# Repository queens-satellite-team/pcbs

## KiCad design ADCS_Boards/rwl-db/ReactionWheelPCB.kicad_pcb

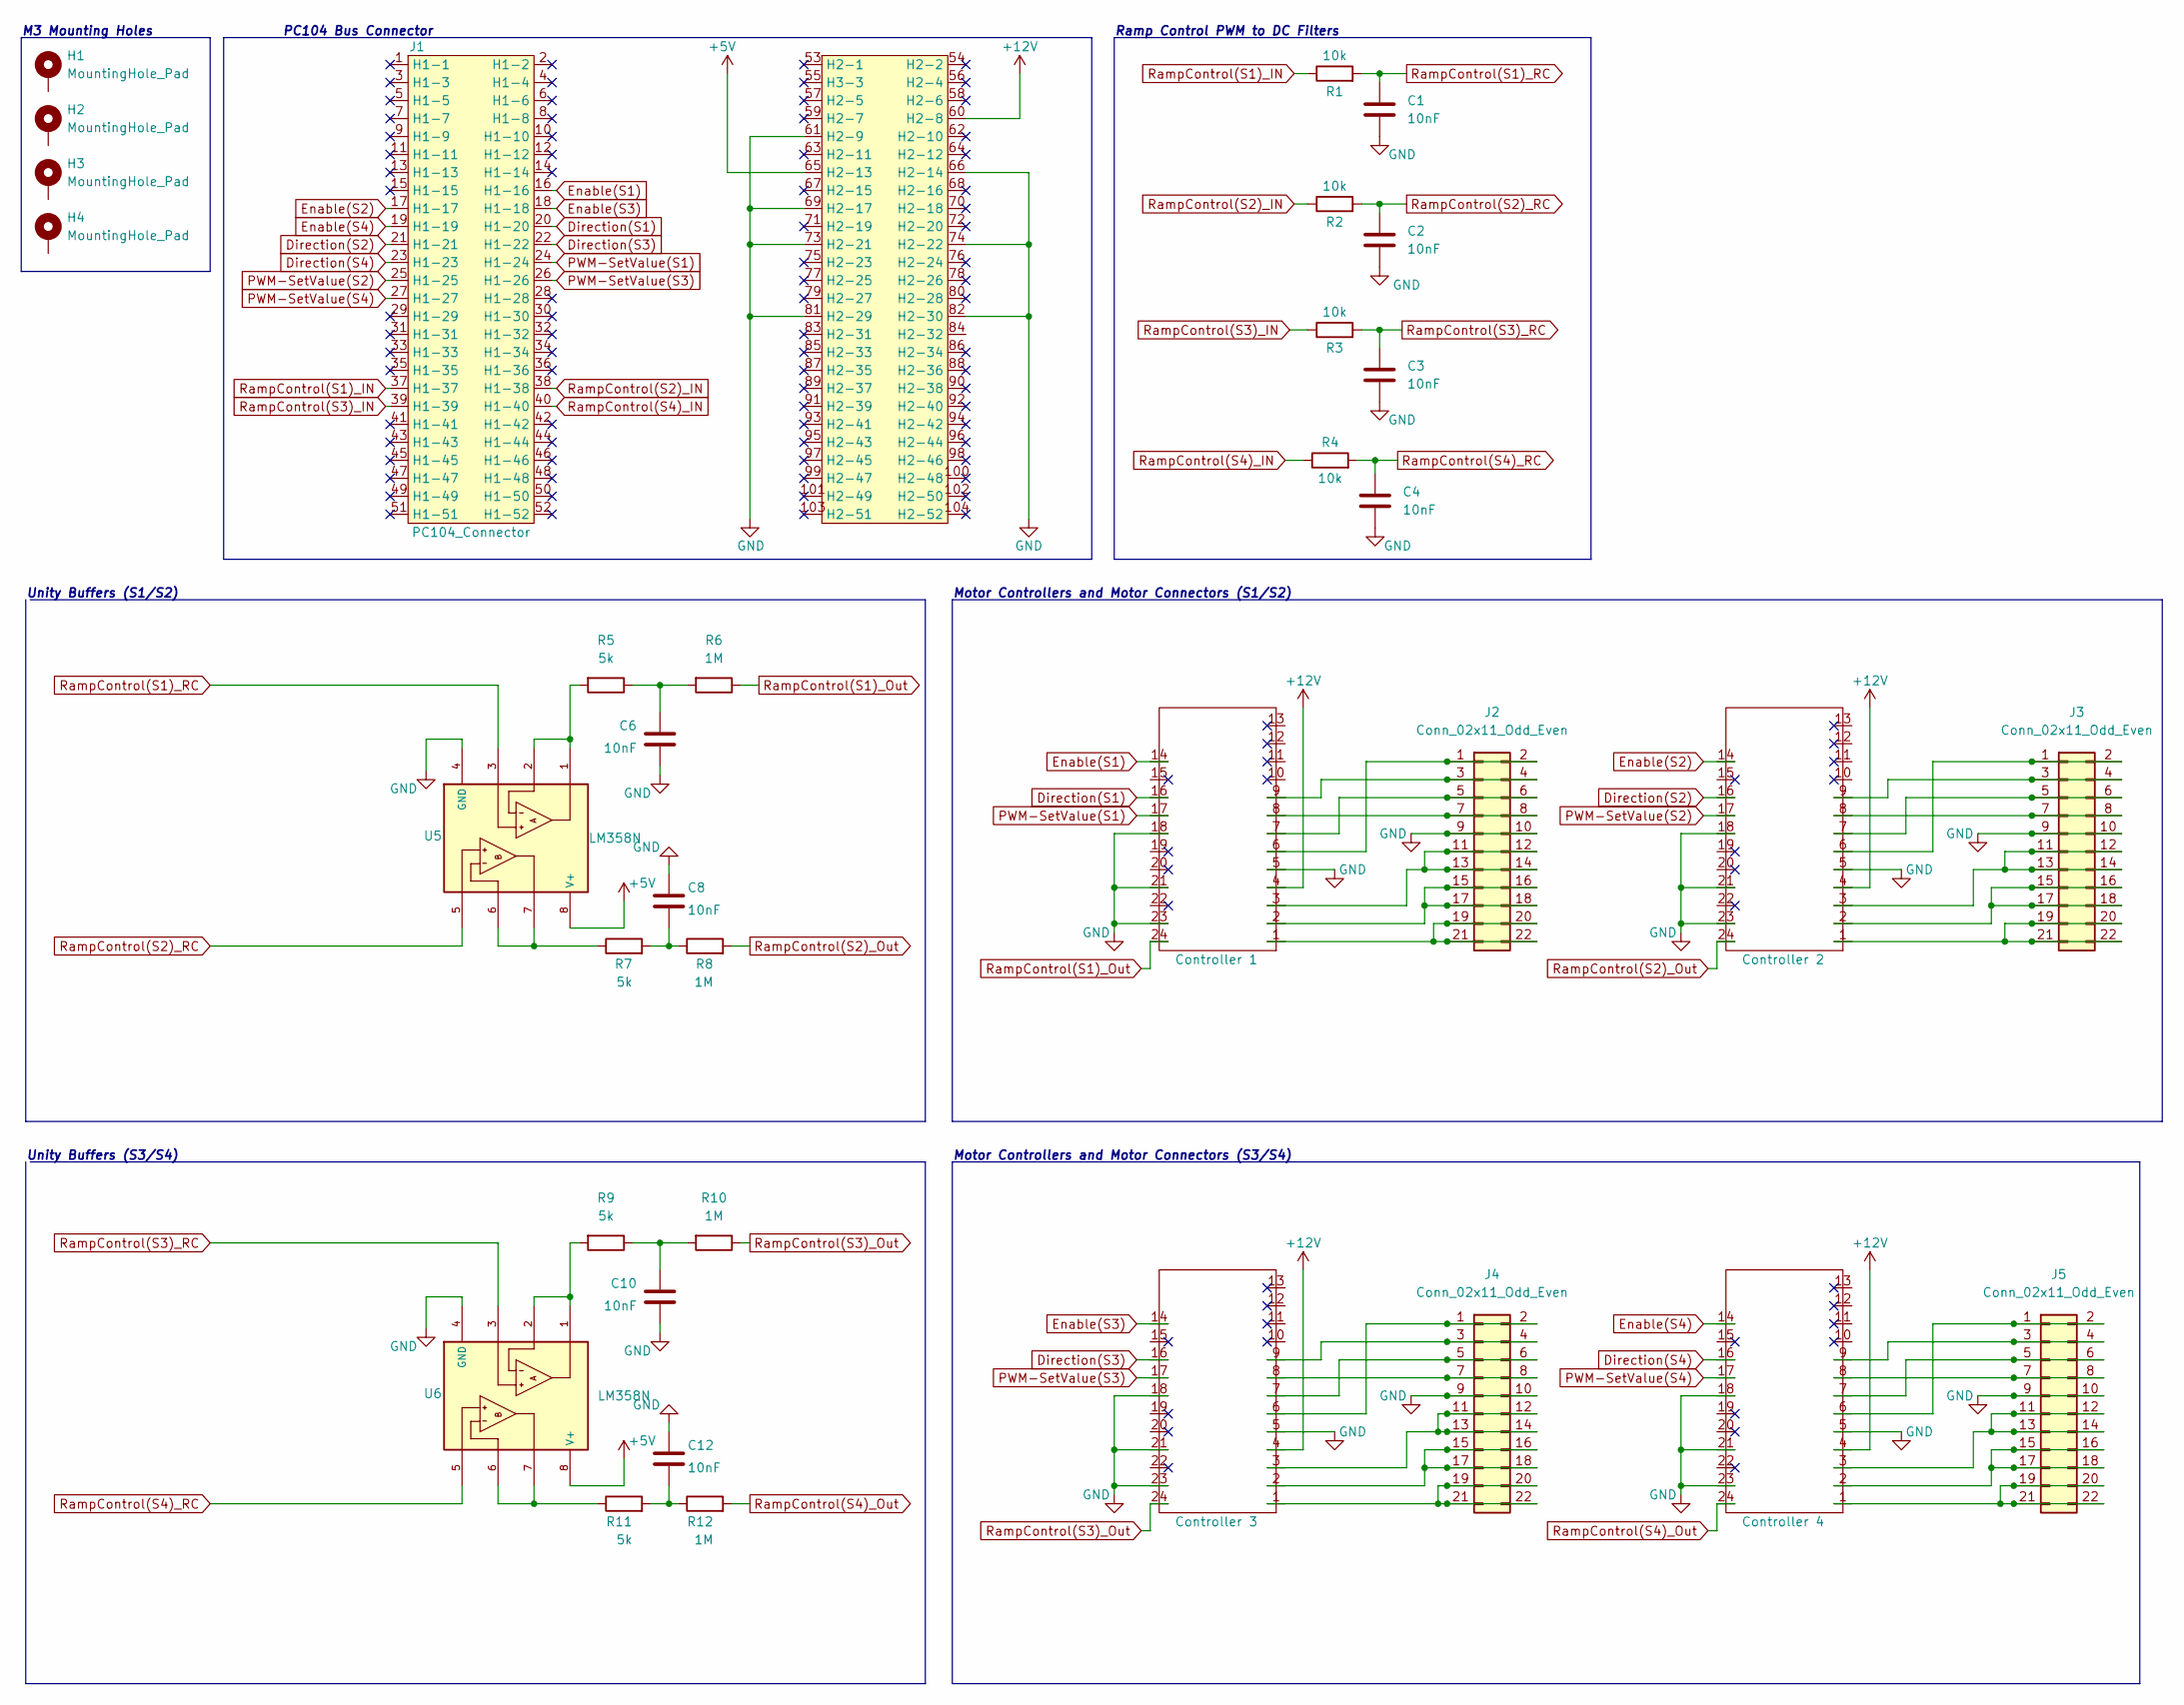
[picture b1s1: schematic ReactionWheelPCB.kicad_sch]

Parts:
C1, C2, C3, C4, C6, C8, C10, C12: 10nF; C_0603_1608Metric
H1, H2, H3, H4: MountingHole_Pad; MountingHole_3.2mm_M3_Pad_TopBottom
J1: PC104_Connector; pc104-connector
J2, J3, J4, J5: Conn_02x11_Odd_Even; 1-1734248-1-reaction-wheel-connector
R1, R2, R3, R4: 10k; R_0603_1608Metric
R5, R7, R9, R11: 5k; R_0603_1608Metric
R6, R8, R10, R12: 1M; R_0603_1608Metric
U1: Controller 1; Escon24.2
U2: Controller 2; Escon24.2
U3: Controller 3; Escon24.2
U4: Controller 4; Escon24.2
U5, U6: LM358N; DIP794W45P254L959H508Q8

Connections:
+5V: J1.65 (H2-13), U5.8 (V+), U6.8 (V+)
+12V: J1.60 (H2-8), U1.4, U2.4, U3.4, U4.4
Direction(S1): J1.20 (H1-20), U1.16
Direction(S2): J1.21 (H1-21), U2.16
Direction(S3): J1.22 (H1-22), U3.16
Direction(S4): J1.23 (H1-23), U4.16
Enable(S1): J1.16 (H1-16), U1.14
Enable(S2): J1.17 (H1-17), U2.14
Enable(S3): J1.18 (H1-18), U3.14
Enable(S4): J1.19 (H1-19), U4.14
GND: C1.1, C2.1, C3.1, C4.1, C6.1, C8.1, C10.1, C12.1, J1.61 (H2-9), J1.66 (H2-14), J1.69 (H2-17), J1.73 (H2-21), J1.74 (H2-22), J1.81 (H2-29), J1.82 (H2-30), J2.9, J2.10, J3.9, J3.10, J4.9, J4.10, J5.9, J5.10, U1.5, U1.18, U1.21, U1.23, U2.5, U2.18, U2.21, U2.23, U3.5, U3.18, U3.21, U3.23, U4.5, U4.18, U4.21, U4.23, U5.4 (GND), U6.4 (GND)
unnamed: C6.2, R5.1, R6.2
unnamed: C8.2, R7.2, R8.1
unnamed: C10.2, R9.1, R10.2
unnamed: C12.2, R11.2, R12.1
unnamed: R5.2, U5.1, U5.2
unnamed: R7.1, U5.6, U5.7
unnamed: R9.2, U6.1, U6.2
unnamed: R11.1, U6.6, U6.7
unnamed: J2.19, J2.20, J2.21, J2.22, U1.1
unnamed: J2.15, J2.16, J2.17, J2.18, U1.2
unnamed: J2.11, J2.12, J2.13, J2.14, U1.3
unnamed: J2.1, J2.2, U1.6
unnamed: J2.5, J2.6, U1.7
unnamed: J2.7, J2.8, U1.8
unnamed: J2.3, J2.4, U1.9
unnamed: J3.19, J3.20, J3.21, J3.22, U2.1
unnamed: J3.15, J3.16, J3.17, J3.18, U2.2
unnamed: J3.11, J3.12, J3.13, J3.14, U2.3
unnamed: J3.1, J3.2, U2.6
unnamed: J3.5, J3.6, U2.7
unnamed: J3.7, J3.8, U2.8
unnamed: J3.3, J3.4, U2.9
unnamed: J4.19, J4.20, J4.21, J4.22, U3.1
unnamed: J4.15, J4.16, J4.17, J4.18, U3.2
unnamed: J4.11, J4.12, J4.13, J4.14, U3.3
unnamed: J4.1, J4.2, U3.6
unnamed: J4.5, J4.6, U3.7
unnamed: J4.7, J4.8, U3.8
unnamed: J4.3, J4.4, U3.9
unnamed: J5.19, J5.20, J5.21, J5.22, U4.1
unnamed: J5.15, J5.16, J5.17, J5.18, U4.2
unnamed: J5.11, J5.12, J5.13, J5.14, U4.3
unnamed: J5.1, J5.2, U4.6
unnamed: J5.5, J5.6, U4.7
unnamed: J5.7, J5.8, U4.8
unnamed: J5.3, J5.4, U4.9
PWM-SetValue(S1): J1.24 (H1-24), U1.17
PWM-SetValue(S2): J1.25 (H1-25), U2.17
PWM-SetValue(S3): J1.26 (H1-26), U3.17
PWM-SetValue(S4): J1.27 (H1-27), U4.17
RampControl(S1)_IN: J1.37 (H1-37), R1.1
RampControl(S1)_Out: R6.1, U1.24
RampControl(S1)_RC: C1.2, R1.2, U5.3
RampControl(S2)_IN: J1.38 (H1-38), R2.1
RampControl(S2)_Out: R8.2, U2.24
RampControl(S2)_RC: C2.2, R2.2, U5.5
RampControl(S3)_IN: J1.39 (H1-39), R3.1
RampControl(S3)_Out: R10.1, U3.24
RampControl(S3)_RC: C3.2, R3.2, U6.3
RampControl(S4)_IN: J1.40 (H1-40), R4.1
RampControl(S4)_Out: R12.2, U4.24
RampControl(S4)_RC: C4.2, R4.2, U6.5

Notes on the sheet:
Motor Controllers and Motor Connectors (S3/S4)
M3 Mounting Holes
Unity Buffers (S3/S4)
Motor Controllers and Motor Connectors (S1/S2)
PC104 Bus Connector
Ramp Control PWM to DC Filters
Unity Buffers (S1/S2)

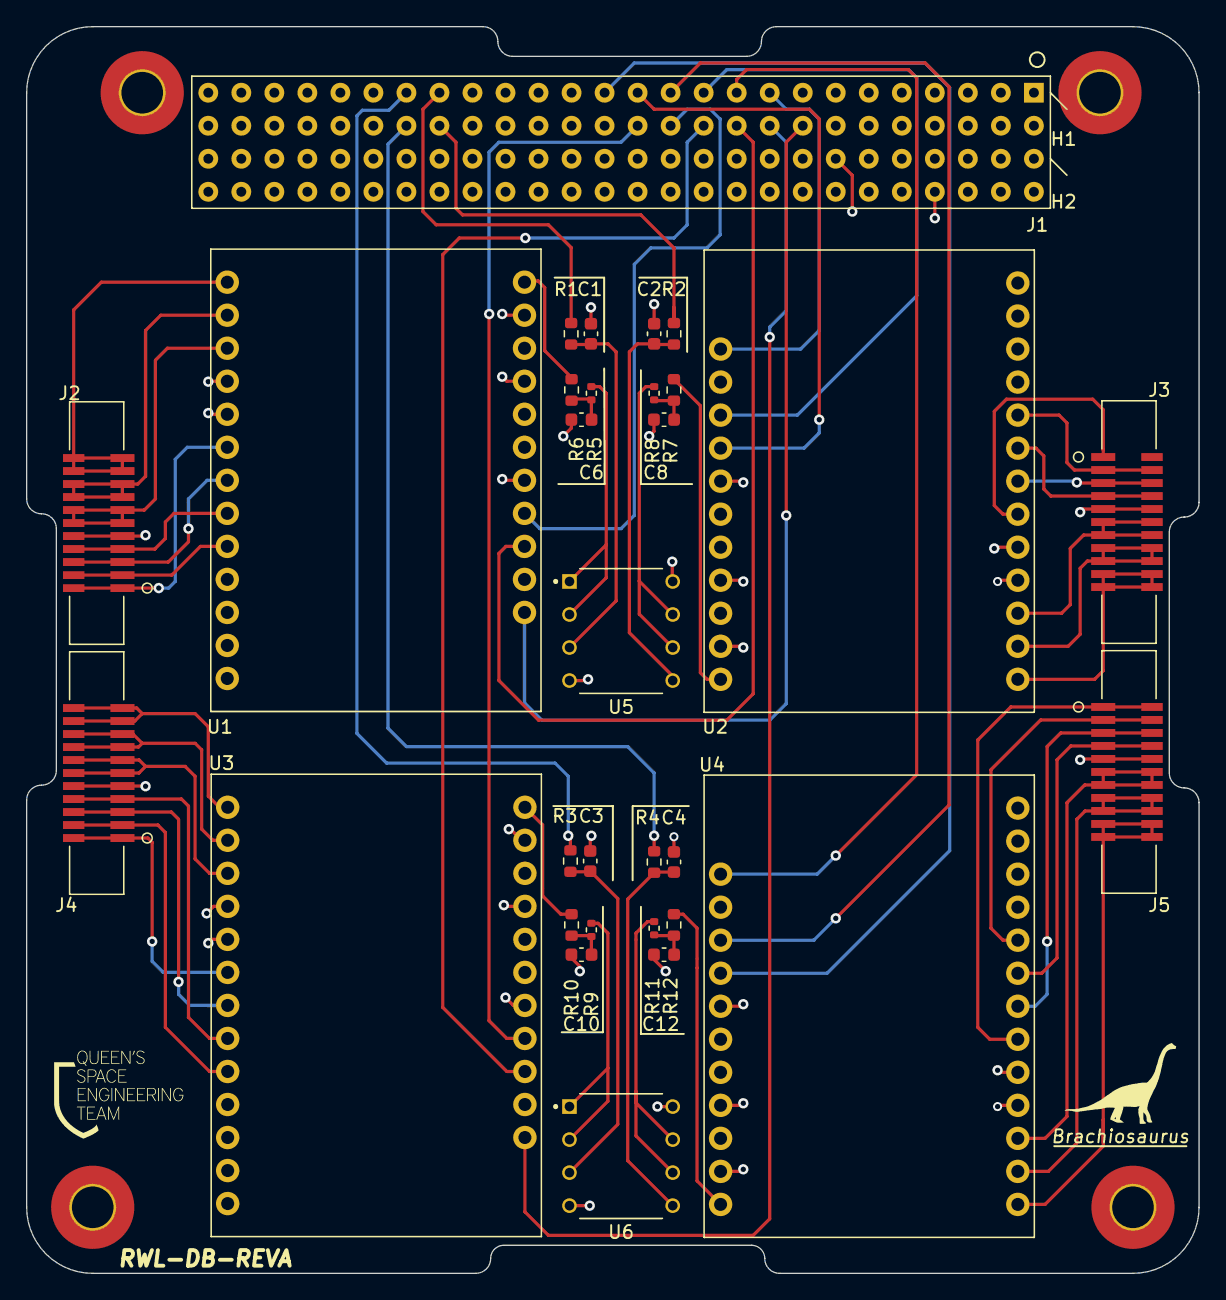
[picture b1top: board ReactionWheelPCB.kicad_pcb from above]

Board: 4 copper layers, 90.2 x 95.9 mm, 36 parts (0 on the bottom side), 63 nets.

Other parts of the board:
Brachiosaurus: LOGO

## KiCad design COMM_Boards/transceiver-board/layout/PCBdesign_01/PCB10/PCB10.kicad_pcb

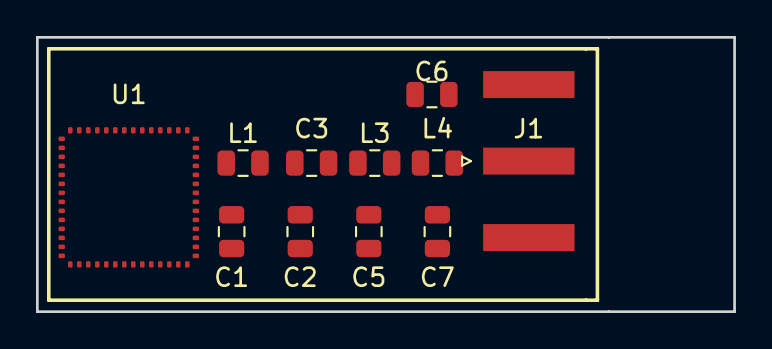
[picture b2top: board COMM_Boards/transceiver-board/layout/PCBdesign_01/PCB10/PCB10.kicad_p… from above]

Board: 2 copper layers, 38.7 x 15.2 mm, 11 parts (0 on the bottom side), 7 nets, no tracks yet.

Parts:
C1, C2: 10pf; C_0805_2012Metric
C3: 2.4pF; C_0805_2012Metric
C5, C6: 15pF; C_0805_2012Metric
C7: 8.2pF; C_0805_2012Metric
J1: Conn_Coaxial_Power; SMA_Amphenol_132289_EdgeMount
L1: 22nH; L_0805_2012Metric
L3, L4: 12nH; L_0805_2012Metric
U1: MKW01Z128

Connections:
+3V3: U1.19, U1.35, U1.43, U1.55
GND: C1.1, C2.2, C5.2, C7.2, U1.3, U1.4, U1.20, U1.36, U1.38, U1.40
unnamed: C1.2, L1.1, U1.42
unnamed: C2.1, C3.2, L1.2, U1.39
unnamed: C3.1, L3.1
unnamed: C5.1, C6.2, L3.2, L4.1
unnamed: C6.1, C7.1, J1.1, L4.2

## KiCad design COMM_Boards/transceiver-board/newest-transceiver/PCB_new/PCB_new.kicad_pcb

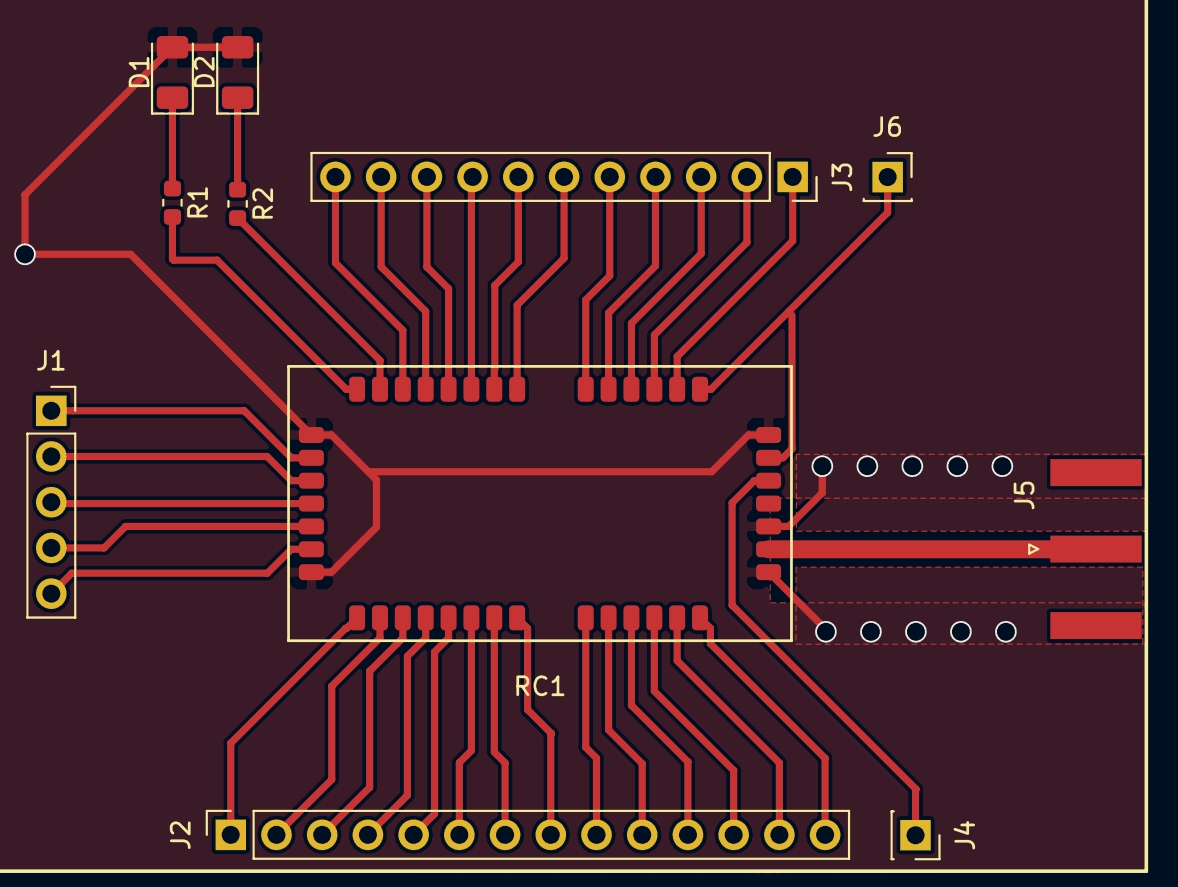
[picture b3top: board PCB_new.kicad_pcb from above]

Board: 2 copper layers, 11 parts (0 on the bottom side), 38 nets.

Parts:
D1, D2: LED; LED_1206_3216Metric
J1: Conn_01x05_Male; PinSocket_1x05_P2.54mm_Vertical
J2: Conn_01x14_Male; PinSocket_1x14_P2.54mm_Vertical
J3: Conn_01x11_Male; PinSocket_1x11_P2.54mm_Vertical
J4, J6: Conn_01x01_Male; PinSocket_1x01_P2.54mm_Vertical
J5: Conn_Coaxial_Power; SMA_Amphenol_132289_EdgeMount
R1, R2: R; R_0603_1608Metric
RC1: RC17xxHP

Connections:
GND: D1.2, D2.2, RC1.1, RC1.7, RC1.8, RC1.10, RC1.14
unnamed: D1.1, R1.1
unnamed: D2.1, R2.1
unnamed: J1.1, RC1.2
unnamed: J1.2, RC1.3
unnamed: J1.3, RC1.4
unnamed: J1.4, RC1.5
unnamed: J1.5, RC1.6
unnamed: J2.1, RC1.15
unnamed: J2.2, RC1.16
unnamed: J2.3, RC1.17
unnamed: J2.4, RC1.18
unnamed: J2.5, RC1.19
unnamed: J2.6, RC1.20
unnamed: J2.7, RC1.21
unnamed: J2.8, RC1.22
unnamed: J2.9, RC1.32
unnamed: J2.10, RC1.34
unnamed: J2.11, RC1.36
unnamed: J2.12, RC1.38
unnamed: J2.13, RC1.40
unnamed: J2.14, RC1.42
unnamed: J3.1, RC1.39
unnamed: J3.2, RC1.37
unnamed: J3.3, RC1.35
unnamed: J3.4, RC1.33
unnamed: J3.5, RC1.31
unnamed: J3.6, RC1.23
unnamed: J3.7, RC1.24
unnamed: J3.8, RC1.25
unnamed: J3.9, RC1.26
unnamed: J3.10, RC1.27
unnamed: J3.11, RC1.28
unnamed: J4.1, RC1.12
unnamed: J5.1, RC1.9
unnamed: R1.2, RC1.30
unnamed: R2.2, RC1.29
VCC: J6.1, RC1.13, RC1.41

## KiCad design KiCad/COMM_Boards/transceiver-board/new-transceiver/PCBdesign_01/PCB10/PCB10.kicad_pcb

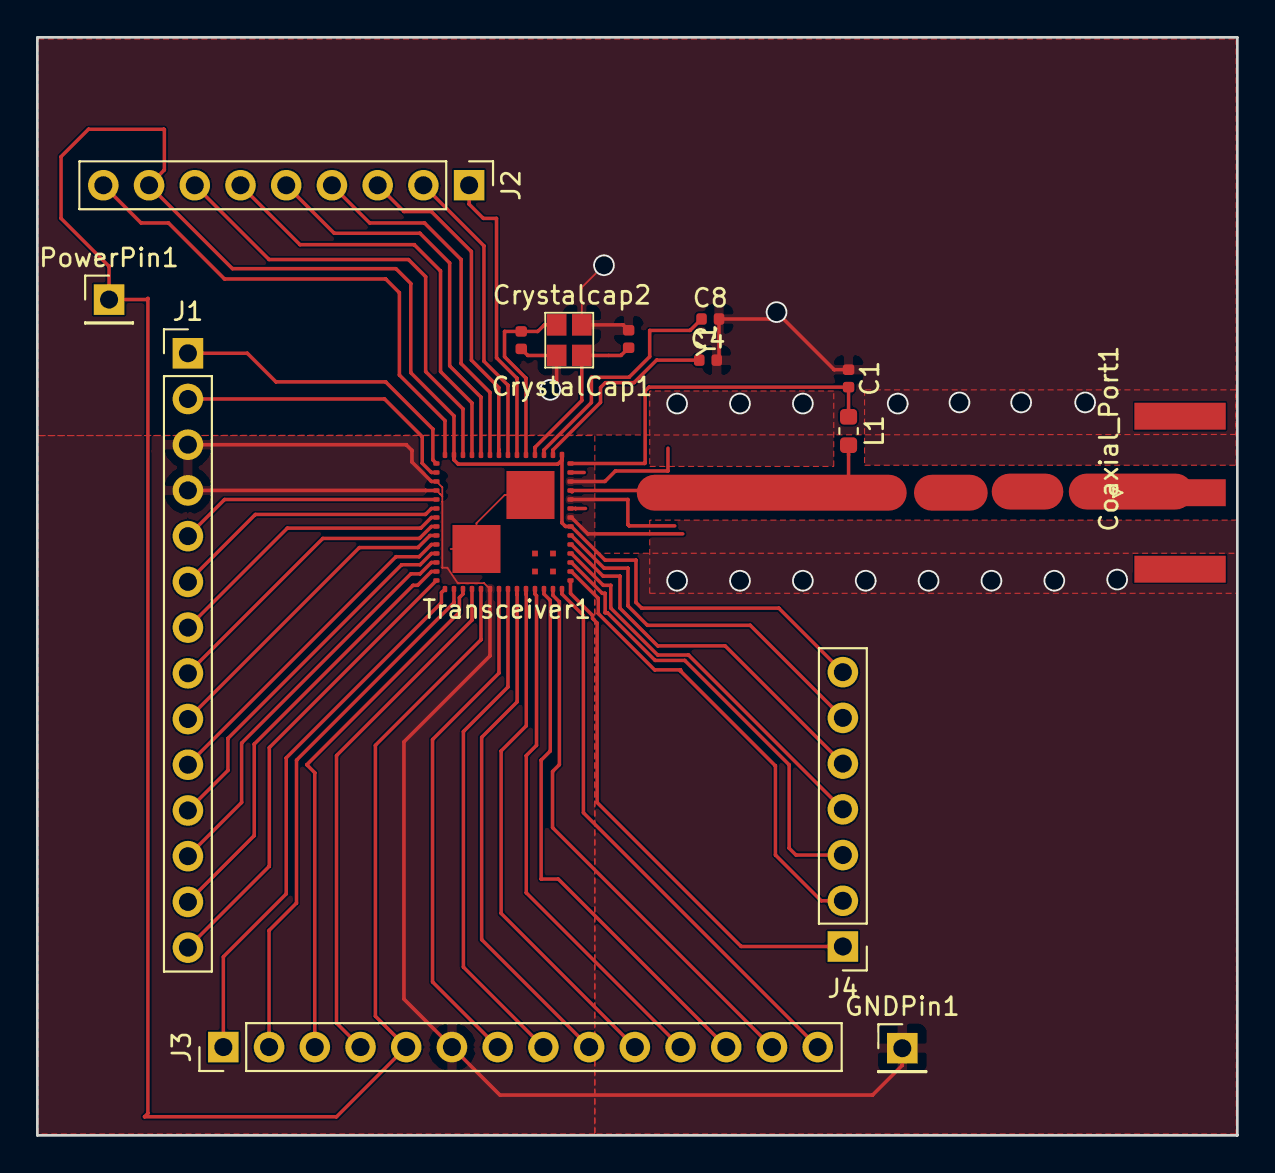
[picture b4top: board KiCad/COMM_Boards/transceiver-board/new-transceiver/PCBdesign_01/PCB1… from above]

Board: 2 copper layers, 66.7 x 61.0 mm, 15 parts (0 on the bottom side), 46 nets.

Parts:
C1: 10pf; C_0402_1005Metric
C4, C8: 100nF; C_0402_1005Metric
Coaxial_Port1: Conn_Coaxial_Power; SMA_Amphenol_132289_EdgeMount
CrystalCap1: CAP; C_0402_1005Metric
Crystalcap2: CAP; C_0402_1005Metric
GNDPin1: Conn_01x01_Male; PinHeader_1x01_P2.54mm_Vertical
J1, J3: Conn_01x14_Male; PinHeader_1x14_P2.54mm_Vertical
J2: Conn_01x09_Male; PinHeader_1x09_P2.54mm_Vertical
J4: Conn_01x07_Male; PinHeader_1x07_P2.54mm_Vertical
L1: 22nH; L_0603_1608Metric
PowerPin1: Conn_01x01_Male; PinHeader_1x01_P2.54mm_Vertical
Transceiver1: MKW01Z128_MKW01Z128; MKW01Z128
Y1: Crystal_GND24; SER3801CT-ND

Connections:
GND: C1.1, C4.2, C8.2, CrystalCap1.2, Crystalcap2.2, GNDPin1.1, J1.3, J1.4, J3.6, Transceiver1.3, Transceiver1.4, Transceiver1.20, Transceiver1.36, Transceiver1.38, Transceiver1.40, Y1.2, Y1.4
unnamed: C1.2, L1.1, Transceiver1.42
unnamed: L1.2, Transceiver1.39
unnamed: C4.1, Transceiver1.44
unnamed: C8.1, Transceiver1.45
unnamed: CrystalCap1.1, Transceiver1.46, Y1.1
unnamed: Crystalcap2.1, Transceiver1.47, Y1.3
unnamed: J1.1, Transceiver1.1
unnamed: J1.2, Transceiver1.2
unnamed: J1.5, Transceiver1.5
unnamed: J1.6, Transceiver1.6
unnamed: J1.7, Transceiver1.7
unnamed: J1.8, Transceiver1.8
unnamed: J1.9, Transceiver1.9
unnamed: J1.10, Transceiver1.10
unnamed: J1.11, Transceiver1.11
unnamed: J1.12, Transceiver1.12
unnamed: J1.13, Transceiver1.13
unnamed: J1.14, Transceiver1.14
unnamed: J2.1, Transceiver1.48
unnamed: J2.2, Transceiver1.49
unnamed: J2.3, Transceiver1.50
unnamed: J2.4, Transceiver1.51
unnamed: J2.5, Transceiver1.52
unnamed: J2.6, Transceiver1.53
unnamed: J2.7, Transceiver1.54
unnamed: J2.9, Transceiver1.56
unnamed: J3.1, Transceiver1.15
unnamed: J3.2, Transceiver1.16
unnamed: J3.3, Transceiver1.17
unnamed: J3.4, Transceiver1.18
unnamed: J3.7, Transceiver1.21
unnamed: J3.8, Transceiver1.22
unnamed: J3.9, Transceiver1.23
unnamed: J3.10, Transceiver1.24
unnamed: J3.11, Transceiver1.25
unnamed: J3.12, Transceiver1.26
unnamed: J3.13, Transceiver1.27
unnamed: J3.14, Transceiver1.28
unnamed: J4.1, Transceiver1.29
unnamed: J4.2, Transceiver1.30
unnamed: J4.3, Transceiver1.31
unnamed: J4.4, Transceiver1.32
unnamed: J4.5, Transceiver1.33
unnamed: J4.6, Transceiver1.34
POWER: J2.8, J3.5, J4.7, PowerPin1.1, Transceiver1.19, Transceiver1.35, Transceiver1.43, Transceiver1.55

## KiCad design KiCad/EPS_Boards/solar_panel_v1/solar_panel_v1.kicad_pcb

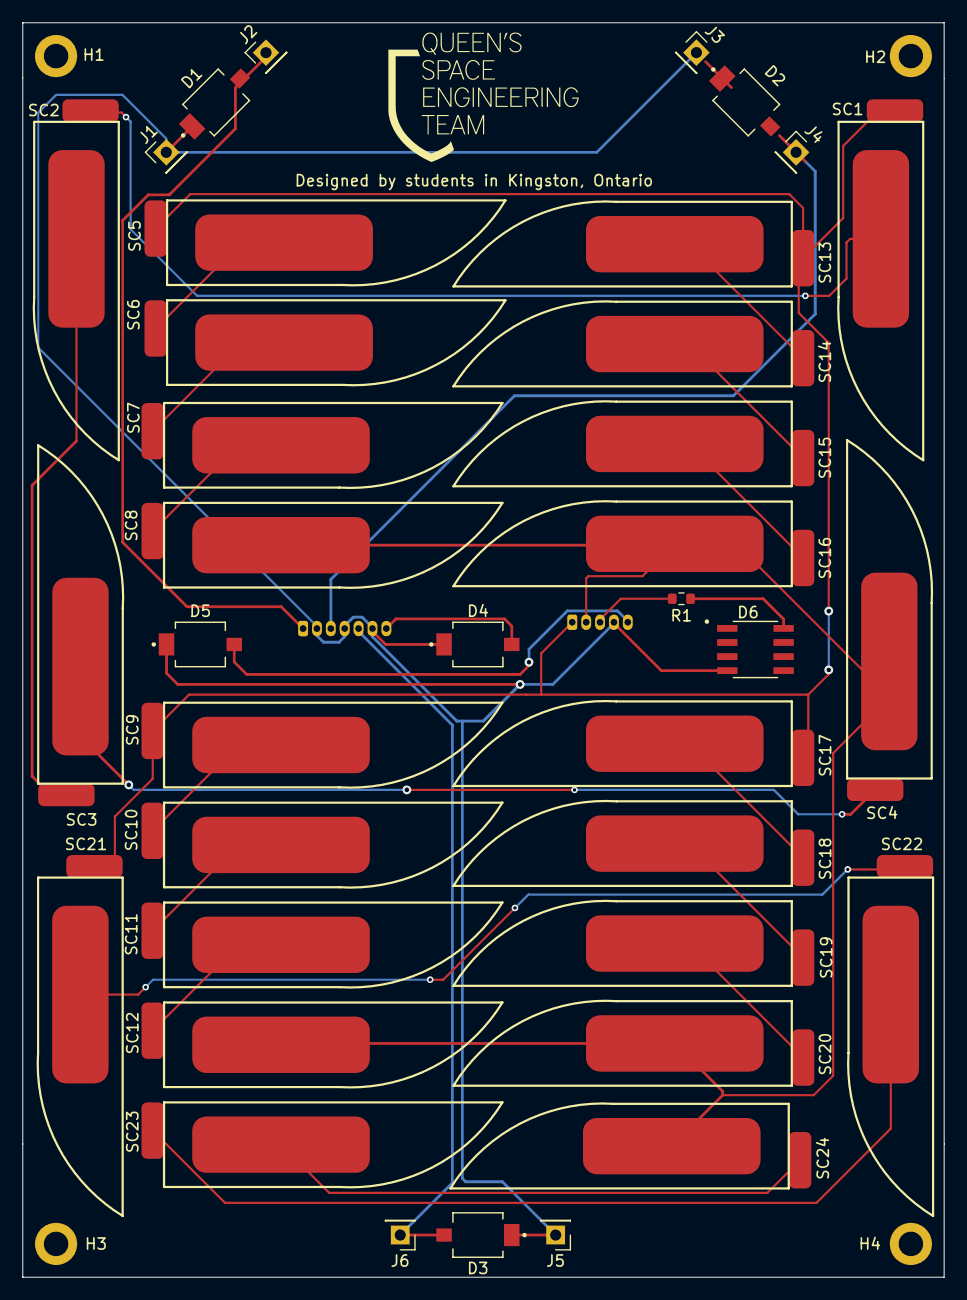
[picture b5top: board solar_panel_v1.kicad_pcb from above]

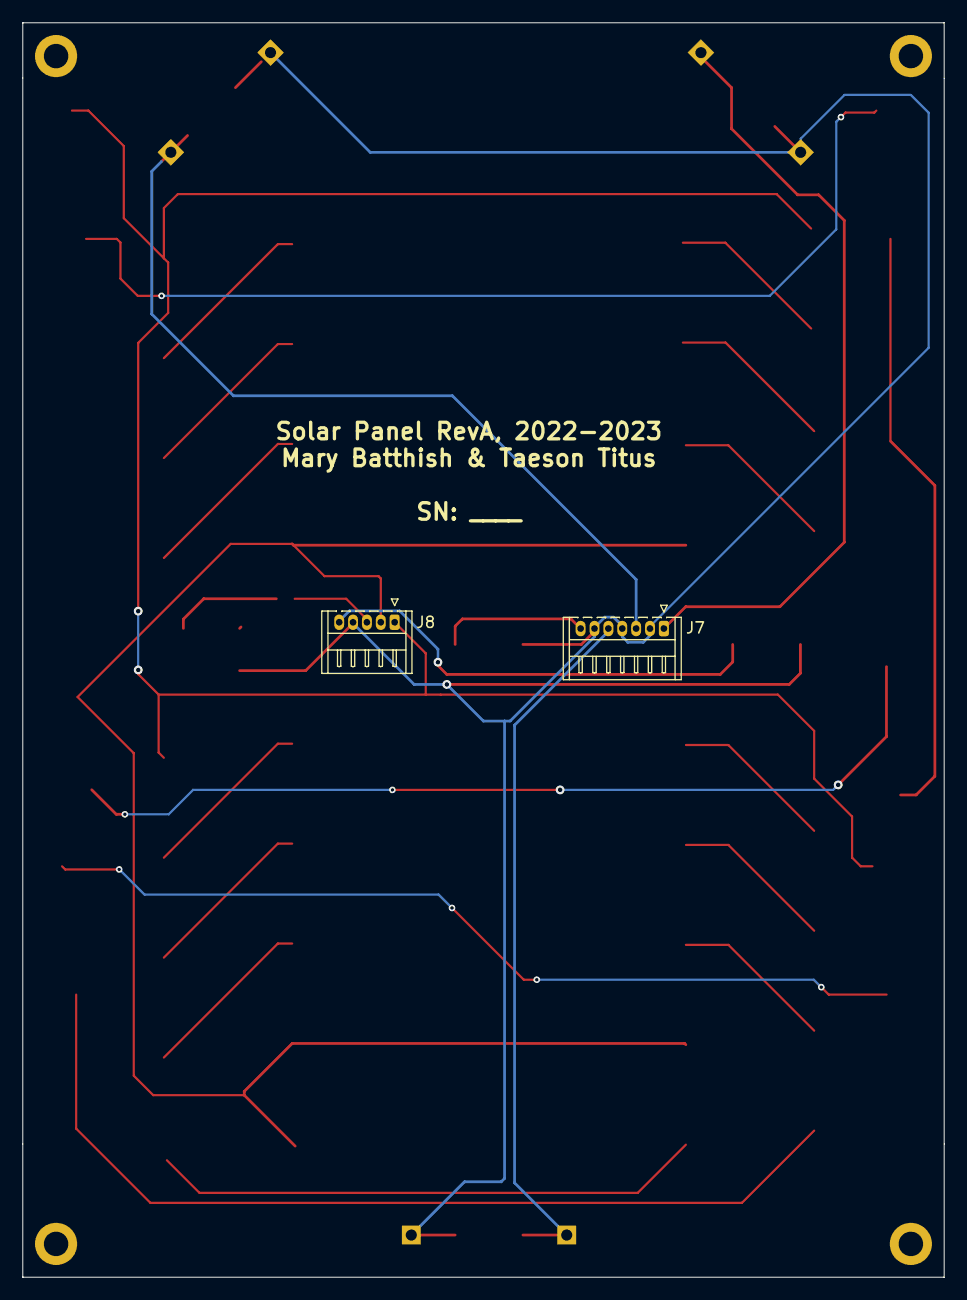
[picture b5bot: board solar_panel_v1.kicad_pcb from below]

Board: 2 copper layers, 83.0 x 113.0 mm, 43 parts (2 on the bottom side), 27 nets.

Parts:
D1, D2, D3, D4, D5: D_Photo; DIO_SFH_2430-Z
D6: D_Temp; SOIC127P600X175-8N
H1, H2, H3, H4: MountingHole; MountingHole_2.2mm_M2_DIN965_Pad
J1, J2, J3, J4, J5, J6: Conn_01x01; PinHeader_1x01_P2.54mm_Vertical
J7: DF13-7P-1.25DS(20); Hirose_DF13-07P-1.25DS_1x07_P1.25mm_Horizontal
J8: DF-13-5P-1.25DS; Hirose_DF13-05P-1.25DS_1x05_P1.25mm_Horizontal
R1: 0; R_0603_1608Metric
SC1, SC2, SC3, SC4, SC5, SC6, SC7, SC8, SC9, SC10, SC11, SC12, SC13, SC14, SC15, SC16, SC17, SC18, SC19, SC20, SC21, SC22, SC23, SC24: Solar_Cell; TrisolX_Solar_Cell

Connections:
ADSC_PD_1: D1.1 (K), J2.1
ADSC_PD_2: D2.1 (K), J4.1
ADSC_PD_3: D3.1 (K), J6.1
ARRAY_PWR: J8.1, SC1.1 (+), SC5.1 (+), SC9.1 (+), SC13.1 (+), SC17.1 (+), SC21.1 (+)
ARRAY_RTN: J8.2, SC4.2 (-), SC8.2 (-), SC12.2 (-), SC16.2 (-), SC20.2 (-), SC24.2 (-)
EPS_PD_1: D5.1 (K), J8.5
EPS_TMP_1: J8.3, R1.2
GND: D1.2 (A), D2.2 (A), D3.2 (A), D4.2 (A), D5.2 (A), D6.4, J1.1, J3.2, J5.1, J7.2, J7.4, J7.6, J8.4
unnamed: D6.8, R1.1
unnamed: SC1.2 (-), SC2.1 (+)
unnamed: SC2.2 (-), SC3.1 (+)
unnamed: SC3.2 (-), SC4.1 (+)
unnamed: SC5.2 (-), SC6.1 (+)
unnamed: SC6.2 (-), SC7.1 (+)
unnamed: SC7.2 (-), SC8.1 (+)
unnamed: SC9.2 (-), SC10.1 (+)
unnamed: SC10.2 (-), SC11.1 (+)
unnamed: SC11.2 (-), SC12.1 (+)
unnamed: SC13.2 (-), SC14.1 (+)
unnamed: SC14.2 (-), SC15.1 (+)
unnamed: SC15.2 (-), SC16.1 (+)
unnamed: SC17.2 (-), SC18.1 (+)
unnamed: SC18.2 (-), SC19.1 (+)
unnamed: SC19.2 (-), SC20.1 (+)
unnamed: SC21.2 (-), SC22.1 (+)
unnamed: SC22.2 (-), SC23.1 (+)
unnamed: SC23.2 (-), SC24.1 (+)

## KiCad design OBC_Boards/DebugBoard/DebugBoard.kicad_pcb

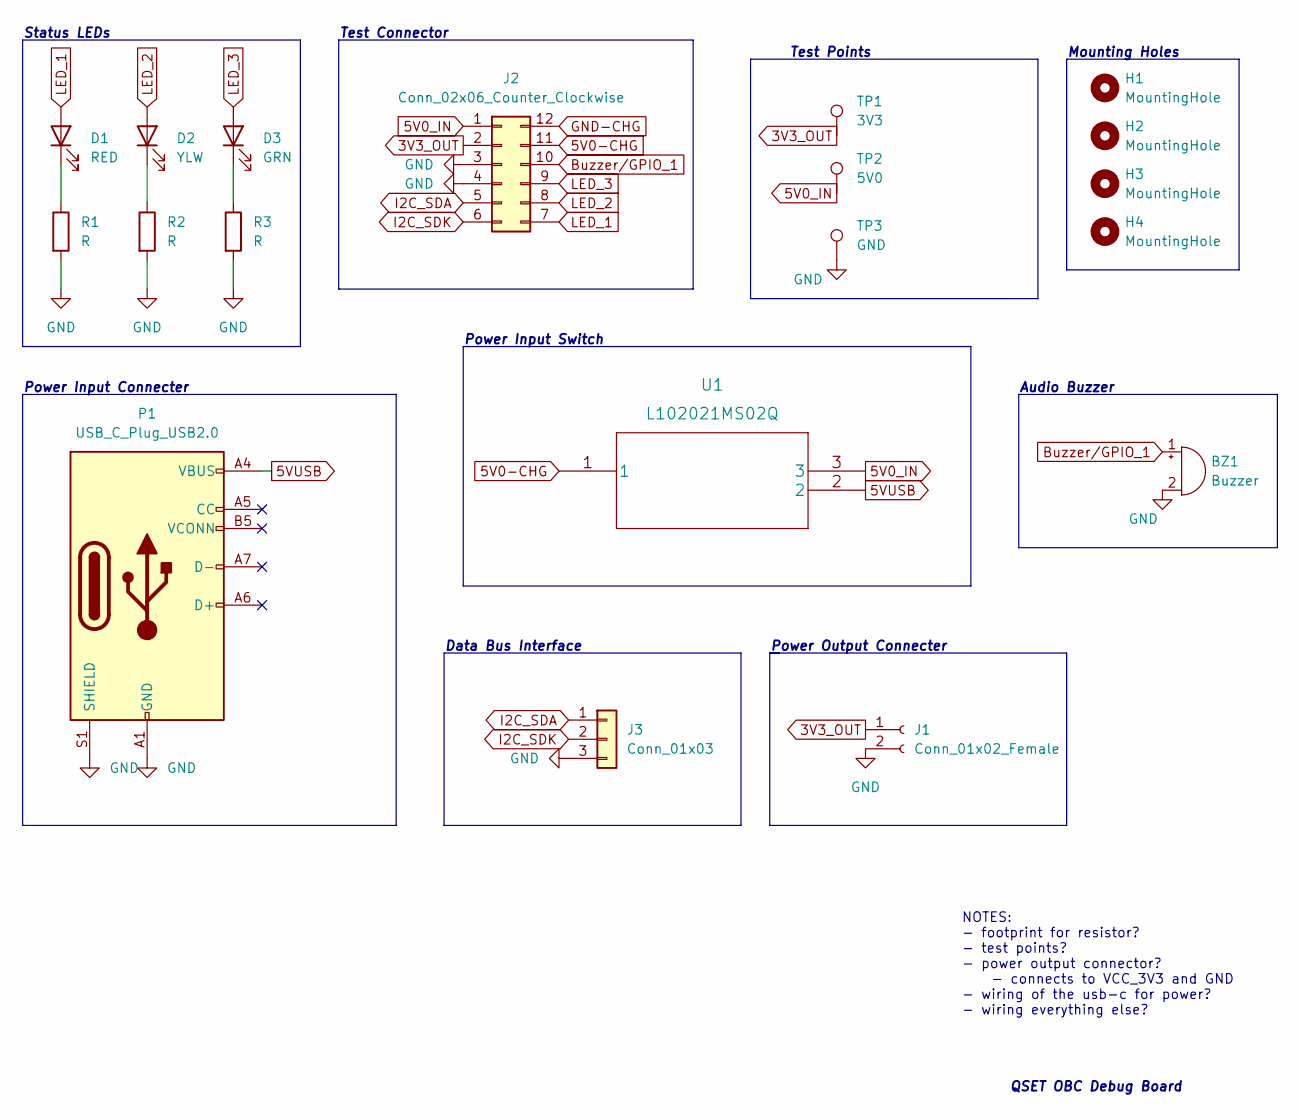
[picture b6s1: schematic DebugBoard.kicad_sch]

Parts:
BZ1: Buzzer; XDCR_CMT-8504-100-SMT-TR
D1: RED; LED_D3.0mm
D2: YLW; LED_D3.0mm
D3: GRN; LED_D3.0mm
H1, H2, H3, H4: MountingHole; MountingHole_2.2mm_M2_Pad
J1: Conn_01x02_Female; PinSocket_1x02_P2.54mm_Horizontal
J2: Conn_02x06_Counter_Clockwise; PinHeader_2x06_P2.54mm_Horizontal
J3: Conn_01x03; PinHeader_1x03_P2.54mm_Horizontal
P1: USB_C_Plug_USB2.0; USB_C_Receptacle_GCT_USB4085
R1, R2, R3: R; R_Axial_DIN0207_L6.3mm_D2.5mm_P7.62mm_Horizontal
TP1: 3V3; TestPoint_Pad_2.0x2.0mm
TP2: 5V0; TestPoint_Pad_2.0x2.0mm
TP3: GND; TestPoint_Pad_2.0x2.0mm
U1: L102021MS02Q

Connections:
3V3_OUT: J1.1, J2.2, TP1.1
5V0-CHG: J2.11, U1.1
5V0_IN: J2.1, TP2.1, U1.3
5VUSB: P1.A4 (VBUS), P1.A9 (VBUS), P1.B4 (VBUS), P1.B9 (VBUS), U1.2
Buzzer/GPIO_1: BZ1.1 (-), J2.10
GND: BZ1.2 (+), J1.2, J2.3, J2.4, J3.3, P1.A1 (GND), P1.A12 (GND), P1.B1 (GND), P1.B12 (GND), P1.S1 (SHIELD), R1.2, R2.2, R3.2, TP3.1
GND-CHG: J2.12
I2C_SDA: J2.5, J3.1
I2C_SDK: J2.6, J3.2
LED_1: D1.2 (A), J2.7
LED_2: D2.2 (A), J2.8
LED_3: D3.2 (A), J2.9
unnamed: D1.1 (K), R1.1
unnamed: D2.1 (K), R2.1
unnamed: D3.1 (K), R3.1

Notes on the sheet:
Status LEDs
Power Output Connecter
Audio Buzzer
Power Input Switch
Mounting Holes
Test Connector
NOTES: - footprint for resistor? - test points? - power output connector? - connects to VCC_3V3 and GND - wiring of the usb-c for power? - wiring everything else?
Power Input Connecter
QSET OBC Debug Board
Data Bus Interface
Test Points

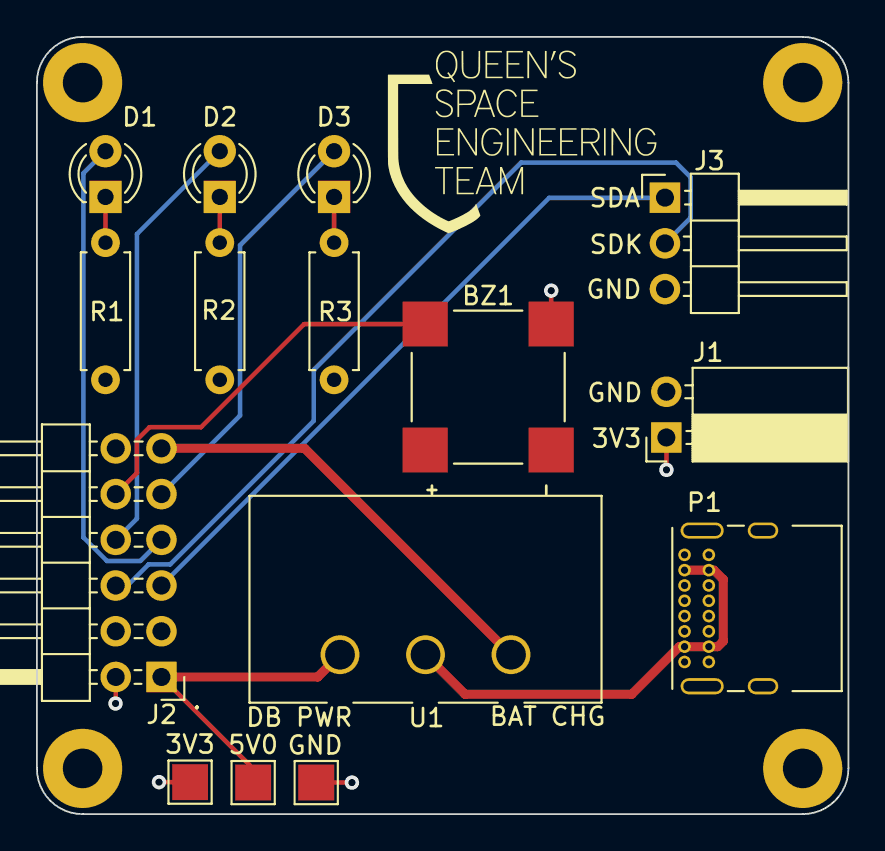
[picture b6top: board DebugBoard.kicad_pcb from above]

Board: 4 copper layers, 45.1 x 43.2 mm, 19 parts (0 on the bottom side), 14 nets.

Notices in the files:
parts and their libraries:
Copyright 2021 Accelerated Designs. All rights reserved.
